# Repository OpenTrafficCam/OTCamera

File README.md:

# OTCamera

OTCamera is a core module of the [OpenTrafficCam framework](https://github.com/OpenTrafficCam) to record videos over multiple days with a custom camera system based on Raspberry Pi Zero W.
In the recorded videos, one can detect and track objects (road users) using [OTVision](https://github.com/OpenTrafficCam/OTVision) or other tools and on the resulting trajectories, one can perform traffic analysis using [OTAnalytics](https://github.com/OpenTrafficCam/OTAnalytics).

Check out the [documentation](https://opentrafficcam.org/OTCamera) for detailed instructions on how to use OTCamera.

We appreciate your support in the form of both code and comments.
First, please have a look at the [contribute](https://opentrafficcam.org/contribute) section of the OpenTrafficCam documentation.

## Development

See [`docs/dev.md`](docs/dev.md) for instructions on setting up a local development environment and running the tests.

## License

This software is licensed under the [GPL-3.0 License](LICENSE).

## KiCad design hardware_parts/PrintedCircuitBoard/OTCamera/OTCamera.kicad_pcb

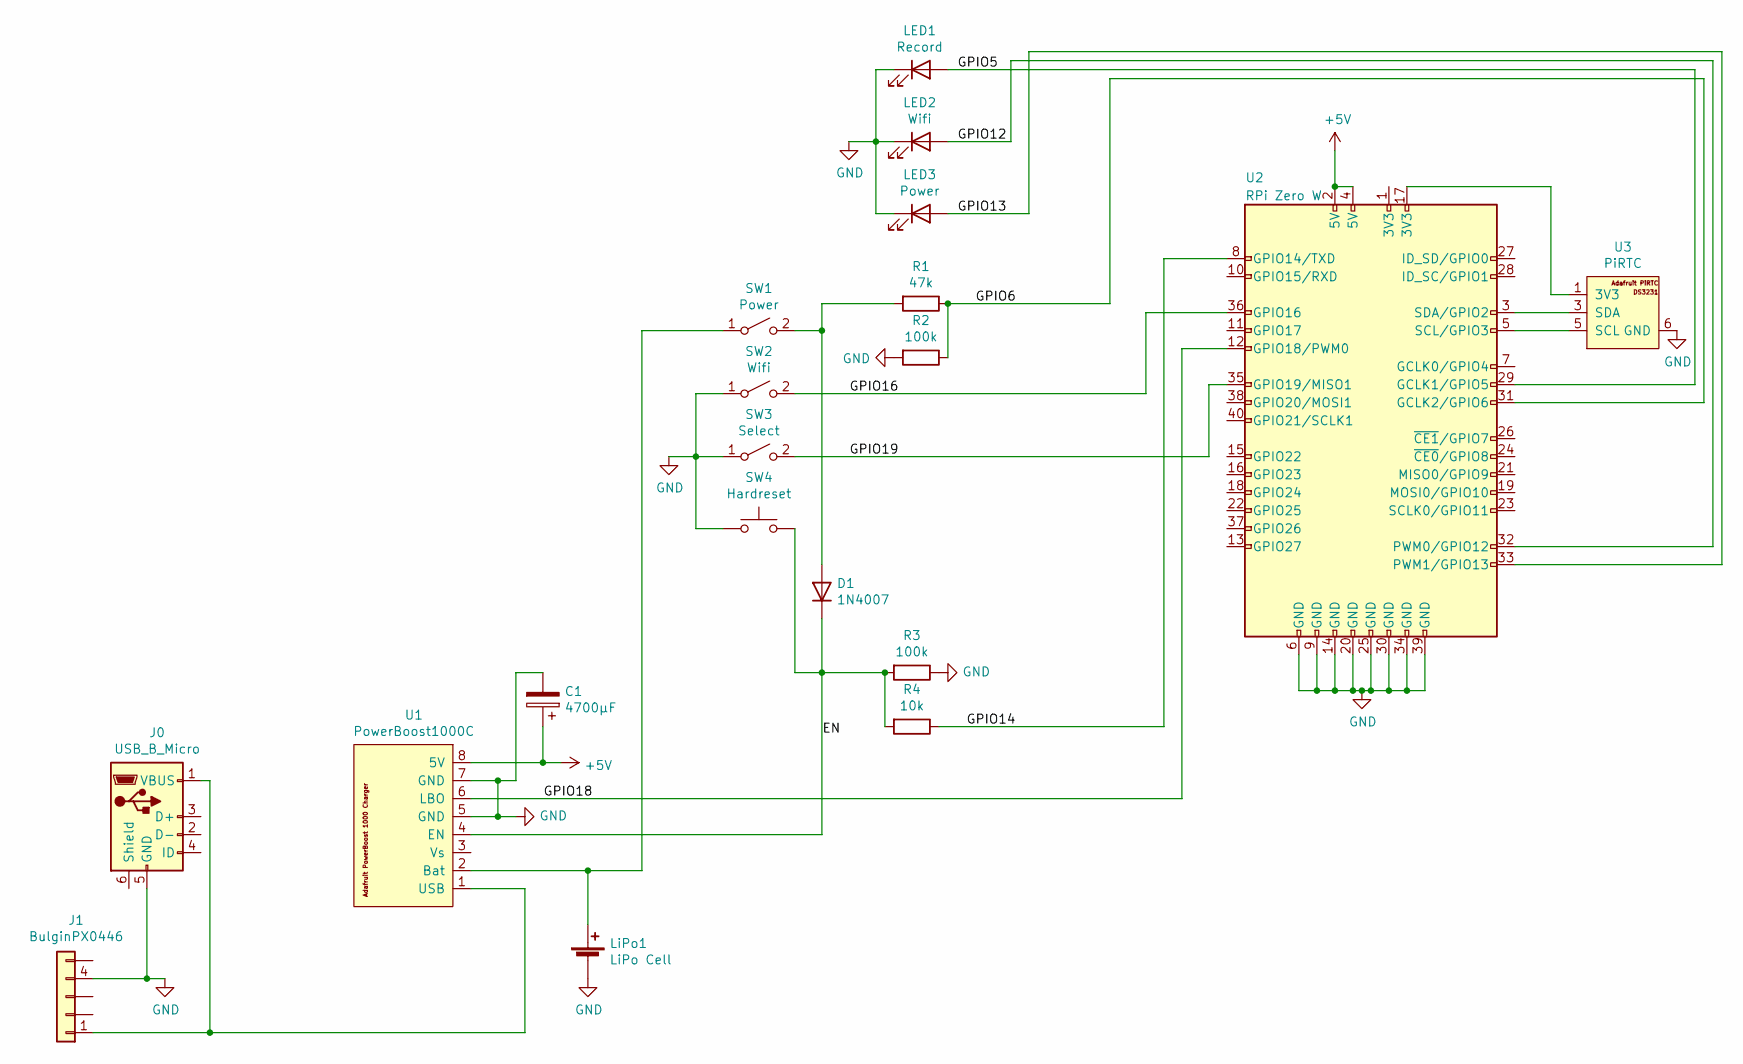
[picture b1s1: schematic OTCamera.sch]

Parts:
C1: 4700µF; CP_Radial_D16.0mm_P7.50mm
D1: 1N4007; D_DO-41_SOD81_P10.16mm_Horizontal
J0: USB_B_Micro; USB_Micro-B_Wuerth_614105150721_Vertical
J1: BulginPX0446; PinSocket_1x05_P2.54mm_Vertical
LED1: Record; PinSocket_1x02_P2.54mm_Vertical
LED2: Wifi; PinSocket_1x02_P2.54mm_Vertical
LED3: Power; PinSocket_1x02_P2.54mm_Vertical
LiPo1: LiPo Cell; Molex_KK-254_AE-6410-02A_1x02_P2.54mm_Vertical
R1: 47k; R_Axial_DIN0207_L6.3mm_D2.5mm_P10.16mm_Horizontal
R2, R3: 100k; R_Axial_DIN0207_L6.3mm_D2.5mm_P10.16mm_Horizontal
R4: 10k; R_Axial_DIN0207_L6.3mm_D2.5mm_P10.16mm_Horizontal
SW1: Power; PinSocket_1x02_P2.54mm_Vertical
SW2: Wifi; PinSocket_1x02_P2.54mm_Vertical
SW3: Select; PinSocket_1x02_P2.54mm_Vertical
SW4: Hardreset; PinSocket_1x02_P2.54mm_Vertical
U1: PowerBoost1000C; PinSocket_1x08_P2.54mm_Vertical
U2: RPi Zero W; PinSocket_2x20_P2.54mm_Vertical
U3: PiRTC; PinHeader_2x03_P2.54mm_Vertical

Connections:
+5V: C1.1, U1.8 (5V), U2.2 (5V), U2.4 (5V)
/EN: D1.1 (K), R3.2, R4.2, SW4.2, U1.4 (EN)
/GPIO5: LED1.2 (A), U2.29 (GCLK1/GPIO5)
/GPIO6: R1.1, R2.1, U2.31 (GCLK2/GPIO6)
/GPIO12: LED2.2 (A), U2.32 (PWM0/GPIO12)
/GPIO13: LED3.2 (A), U2.33 (PWM1/GPIO13)
/GPIO14: R4.1, U2.8 (GPIO14/TXD)
/GPIO16: SW2.2 (B), U2.36 (GPIO16)
/GPIO18: U1.6 (LBO), U2.12 (GPIO18/PWM0)
/GPIO19: SW3.2 (B), U2.35 (GPIO19/MISO1)
GND: C1.2, J0.5 (GND), J1.4 (GND), LED1.1 (K), LED2.1 (K), LED3.1 (K), LiPo1.2 (-), R2.2, R3.1, SW2.1 (A), SW3.1 (A), SW4.1, U1.5 (GND), U1.7 (GND), U2.6 (GND), U2.9 (GND), U2.14 (GND), U2.20 (GND), U2.25 (GND), U2.30 (GND), U2.34 (GND), U2.39 (GND), U3.6 (GND)
unnamed: D1.2 (A), R1.2, SW1.2 (B)
unnamed: J0.1 (VBUS), J1.1 (5V), U1.1 (USB)
unnamed: LiPo1.1 (+), SW1.1 (A), U1.2 (Bat)
unnamed: U2.3 (SDA/GPIO2), U3.3 (SDA)
unnamed: U2.5 (SCL/GPIO3), U3.5 (SCL)
unnamed: U2.17 (3V3), U3.1 (3V3)

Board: 2 copper layers, 19 parts (0 on the bottom side), 17 nets, no tracks yet.

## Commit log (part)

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2024-02-20 config vars for server and port
2024-02-22 Add logging output
2024-02-22 Change server ip
2024-05-06 Bump picamerax from 21.9.8 to 24.3.21
    Bumps [picamerax](https://github.com/labthings/picamerax) from 21.9.8 to 24.3.21.
    - [Release notes](https://github.com/labthings/picamerax/releases)
    - [Changelog](https://github.com/labthings/picamerax/blob/master/docs/changelog.rst)
    - [Commits](https://github.com/labthings/picamerax/compare/21.9.8...24.3.21)
    ---
    updated-dependencies:
2024-05-06 Bump beautifulsoup4 from 4.12.2 to 4.12.3
    Bumps [beautifulsoup4](https://www.crummy.com/software/BeautifulSoup/bs4/) from 4.12.2 to 4.12.3.
    ---
    updated-dependencies:
    - dependency-name: beautifulsoup4
    dependency-type: direct:production
    update-type: version-update:semver-patch
2024-05-21 --- updated-dependencies: - dependency-name: requests dependency-type: direct:production ...
2024-05-27 Bump requests from 2.31.0 to 2.32.2
    Bumps [requests](https://github.com/psf/requests) from 2.31.0 to 2.32.2.
    - [Release notes](https://github.com/psf/requests/releases)
    - [Changelog](https://github.com/psf/requests/blob/main/HISTORY.md)
    - [Commits](https://github.com/psf/requests/compare/v2.31.0...v2.32.2)
    ---
    updated-dependencies:
2024-06-03 Bump requests from 2.31.0 to 2.32.3
    Bumps [requests](https://github.com/psf/requests) from 2.31.0 to 2.32.3.
    - [Release notes](https://github.com/psf/requests/releases)
    - [Changelog](https://github.com/psf/requests/blob/main/HISTORY.md)
    - [Commits](https://github.com/psf/requests/compare/v2.31.0...v2.32.3)
    ---
    updated-dependencies:
2025-05-22 Add update_precommit script
2025-05-22 Sort entries in requirements.txt
2025-05-22 Add missing newline in LED module docstring
    A newline was added to improve code readability and adhere to style guidelines in the LED module. No functional changes were made. Additionally, the bootstrap CSS file remained unchanged.
2025-05-22 Sort import
2025-05-22 Remove not needed setup.py and setup.cfg
    setup.py has been replaced with pyproject.toml
2025-05-22 Add pre-commit config file
2025-05-23 Add type hints to functions and improve code consistency
    Refactored the codebase to add or enhance type annotations for functions and methods, improving type safety and readability. Addressed minor inconsistencies such as variable naming, misspellings, and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
2025-05-23 Lower Python version requirement and add mypy overrides.
    Reduced the minimum Python version requirement to >=3.9 since OTCamera runs on Raspberry Pi Zero W.
2025-05-23 Refactor type hints and update dependencies.
    Replaced Python 3.10+ pipe syntax for Union with explicit Union since we are working with python3.9. Added `opencv-python` to `requirements-dev.txt` and pre-commit additional dependencies. Updated pr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
2025-05-23 Fix log file sorting functionality to handle files without timestamp contained in file name
2025-05-23 Refactor type hints and fix import formatting.
    Updated type hints for `parse_args` and `main` to `None` for clarity and consistency. Adjusted
2025-06-17 Update docstring format in `camera.py` for improved readability and consistency
2025-06-17 Refactor existing picamerax's PiCamera class to own PiCameraX implementing newly introduced Camera interface
2025-06-17 Define initial version constant for OTCamera module.
2025-06-17 Rename `Camera` to `CameraController` and update references across the project.
2025-06-18 Introduce `CameraProvider` for dynamic camera type management and refactor `CameraController` to use the `Camera` interface.
2025-06-25 Update super linter to v7
2025-06-25 Try fixing differing behavior of isort in super-linter
2025-06-25 Format imports
2025-06-25 Lint template.html
2025-06-25 Fix lint errors in usb_flash_drive_copy.py
2025-06-25 Fix lint error in pre-commit config
2025-06-25 Make wifistart executable to fix lint error
2025-06-25 Set permissions for linter GitHub workflow
2025-07-22 Add custom scalar style override to enforce double quotes in YAML serialization
2025-07-22 Add install scripts
2025-07-22 Indent template.html content to follow consistent code style
2025-07-22 Fix indentation
2025-10-24 OP#8760:
    Add config option to send preview image to external server
2025-10-24 OP#8760:
    First attempt to send the preview image to an external URL
2025-11-10 OP#8760: Send preview image as base64 image
2025-11-10 OP#8760: Add send preview to url to example config
2025-11-10 OP#8760: Reorder imports
2025-11-10 OP#8760: Fix import order
2025-11-18 OP#8900: Upload video files to server after each video split
2025-11-18 OP#8900: Update config variables
2025-11-18 OP#8900: Fix imports
2025-11-19 OP#8900: Remove unused FTP server-related components and utility classes
2025-11-19 OP#8900: Ensure FTP server connection is closed after video upload
2025-11-19 OP#8900: Add `SERVER_SOURCE` configuration for server upload settings
2025-11-19 OP#8900: Add commented out example configuration for server upload settings in user_config
2025-11-19 OP#8900: Sort imports
2025-11-20 OP8900: Upload previous segment after split to avoid 0-byte files
    PiCamera’s `split_recording(new_file)` immediately switches the encoder to the
    new file. We were attempting to upload the just-created file name, resulting in
    near-0-byte uploads.
2025-11-20 OP#8900: Fix line breaks
2025-12-19 Fix link case sensitivity in README.md
2026-01-27 OP#7975: Add `CameraClosedError` exception class to handle specific camera closure errors
2026-01-29 Implemented the picamera2 module
2026-02-10 Add power button pull-up configuration.
2026-02-25 Initial commit OTCamera v2: New PCB, power monitoring via ADC, picamera2 lib
2026-02-26 added ADC_ENABLE in config
2026-02-26 fixed adc divisor
2026-02-26 Implement DRC strength via rpi.contrast tuning fixed rfkill permission
2026-02-26 fix tuning file loading by detecting sensor model
2026-02-26 apply camera rotation transform in video configuration
2026-03-04 fix: apply video output resolution in picamera2 encoder
2026-03-04 ● fix: allow flexible exposure times in picamera2 by using FrameDurationLimits as upper bound
2026-03-05 added claude.md
2026-04-02 updatet user config exmaple
2026-04-08 Install picamera on Linux only
2026-04-08 Added docker-compose.yml for local S3
2026-04-08 First threaded s3 upload implementation
2026-04-09 Refactor S3 upload, add integration test
2026-04-09 Handle required parameters when parsing config
2026-04-09 Log S3Upload provisioning
2026-04-09 fix: variable assignment
2026-04-10 Downgrade opencv-python-headless
2026-04-10 fix: more speaking logs
2026-04-13 refactor: restructure upload system and add delete-after-upload feature
    - **Upload interface**: Split `upload()` into orchestration layer and `_do_upload()` implementation. Added `on_success` callback to invoke after successful uploads.
    - **Exception hierarchy**: Renamed `UploadUnavailableError` to `BackendUnavailableError`. Created `UploadError` base class for upload completion failures; `BackendUnavailableError` now inherits from 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
    - **Delete after upload**: Added `delete_after_upload` config option. Created `delete_file()` helper. Integrated into FTP and S3 upload backends via `on_success` callback.
    - **S3 configuration**: Removed `S3Upload.from_config()` classmethod. Now con
2026-04-13 refactor(upload): remove enable flags from upload configs
    Upload configurations are now optional fields. When present, the
    config is considered enabled.
    - Remove `enable` field from `FtpUploadConfig` and `S3Config`
    - Make `ftp_upload` and `s3_upload` optional in `Config`
    - Simplify upload provider logic to check config presence
    - Remove redundant conditional credential validators
2026-04-13 fix: add ignore comment for editorconfig-checker
2026-04-13 chore: fix line length
2026-04-13 ci: add ignore files
2026-04-13 ci: disable lint for md & language
2026-04-15 fix: only import what is needed from abc
2026-04-17 feat: extract resource closing
2026-04-17 feat: added log message on successful s3 upload
2026-04-20 fix: use key-prefix directly
2026-04-22 refactor: separate mkdocs from other docs
2026-04-22 chore: add missing --- to mkdocs.yml
2026-04-22 chore: remove comment (UTC confirmed)
2026-04-22 doc: Update AGENTS.md re imports
2026-04-22 feat: add rabbitmq to docker-compose.yml
2026-04-22 feat: add pika to dependencies
2026-04-24 fix: more specific imports
2026-04-24 feat: add ssl config parameter
2026-04-24 refactor: use publisher thread
2026-04-27 doc: add more docstrings to rabbitmq notifier
2026-04-27 fix: revert changes to listen adresses
2026-04-27 fix: set default port for rabbitmq to ssl port
2026-04-27 chore: fix formatting
2026-04-27 fix: use filename instead of path in test
2026-04-27 doc: explanatory comment for original filename
2026-04-27 refactor: move event creation into upload results
2026-04-28 refactor: rename filename to filepath
2026-04-28 chore: formatting
2026-05-08 add explanatory comment about old and new filenames
2026-05-13 Move dependencies to pyproject.toml
2026-05-20 use markers instead of optional dependencies
2026-05-21 OP#9580: Enforce missing type-stubs to be added to be ignored or added manually
    Require user to explicitly add or ignore missing type stubs by adding them either to
    the requirements-dev.txt on add or to the tool.mypy.overrides -> module section on ignore.
    For this to work mypy has been configured to raise errors on missing
    imports.
    Therefore the update_precommit.py script has been removed.
    Pre-commit now uses the local mypy found in the venv folder.
2026-05-22 cast fake_bus to adc._bus
2026-05-27 add ruff config: lint google-style docstrings
2026-05-27 bump Python minimum version
2026-05-27 pre-commit: don't force venv
2026-05-27 pin to fixed versions
2026-05-27 add boto3 dependency
2026-05-27 loosened constraint on types-psutil
2026-05-27 bumped requests
2026-05-27 extend ignore imports for smbus2 and cv2
2026-05-27 added constructor args to docstring
2026-05-27 use Path.unlink() instead of os.remove()
2026-05-27 fix S3Upload docstrings
2026-05-28 exclude tests/ from being linted with pydocstyle
2026-05-28 formatting
2026-05-29 work on docstrings
2026-06-01 switch to ruff for linting & formatting
2026-06-01 fix uv export
2026-06-01 regenerate lock files
2026-06-01 add pika to dependencies
2026-06-01 add service-file and entrypoint
2026-06-01 wip: first version of network monitoring
2026-06-01 extend service file
2026-06-01 remove duplicate file
2026-06-01 remove reconnect implementations
2026-06-01 refactor, split into modules
2026-06-01 fix documentation
2026-06-02 modify help-text
2026-06-02 implement reviewer feedback
2026-06-02 fix Pi version in documentation
2026-06-02 remove docstring linting from select
2026-06-08 Bump actions/checkout from 4 to 6
    Bumps [actions/checkout](https://github.com/actions/checkout) from 4 to 6.
    - [Release notes](https://github.com/actions/checkout/releases)
    - [Changelog](https://github.com/actions/checkout/blob/main/CHANGELOG.md)
    - [Commits](https://github.com/actions/checkout/compare/v4...v6)
    ---
    updated-dependencies:
2026-06-08 Bump requests from 2.31.0 to 2.34.2
    Bumps [requests](https://github.com/psf/requests) from 2.31.0 to 2.34.2.
    - [Release notes](https://github.com/psf/requests/releases)
    - [Changelog](https://github.com/psf/requests/blob/main/HISTORY.md)
    - [Commits](https://github.com/psf/requests/compare/v2.31.0...v2.34.2)
    ---
    updated-dependencies:
2026-06-08 Bump psutil from 5.9.5 to 7.2.2
    Bumps [psutil](https://github.com/giampaolo/psutil) from 5.9.5 to 7.2.2.
    - [Changelog](https://github.com/giampaolo/psutil/blob/master/docs/changelog.rst)
    - [Commits](https://github.com/giampaolo/psutil/compare/v5.9.5...v7.2.2)
    ---
    updated-dependencies:
    - dependency-name: psutil
2026-06-08 Bump art from 6.1 to 6.5
    Bumps [art](https://github.com/sepandhaghighi/art) from 6.1 to 6.5.
    - [Release notes](https://github.com/sepandhaghighi/art/releases)
    - [Changelog](https://github.com/sepandhaghighi/art/blob/master/CHANGELOG.md)
    - [Commits](https://github.com/sepandhaghighi/art/compare/v6.1...v6.5)
    ---
    updated-dependencies:
2026-06-09 add metrics logging module
2026-06-10 finish docstring
2026-06-10 add fallback on error
2026-06-18 Debounce buttons with gpioszero's bounce_time
2026-06-22 Bump actions/checkout from 4 to 7
    Bumps [actions/checkout](https://github.com/actions/checkout) from 4 to 7.
    - [Release notes](https://github.com/actions/checkout/releases)
    - [Changelog](https://github.com/actions/checkout/blob/main/CHANGELOG.md)
    - [Commits](https://github.com/actions/checkout/compare/v4...v7)
    ---
    updated-dependencies:
2026-06-23 fix dev dependencies
2026-06-23 removed isort, added isort rules to ruff
2026-06-23 update documentation
2026-06-26 add missing bounce_time parameter to FakeButton
